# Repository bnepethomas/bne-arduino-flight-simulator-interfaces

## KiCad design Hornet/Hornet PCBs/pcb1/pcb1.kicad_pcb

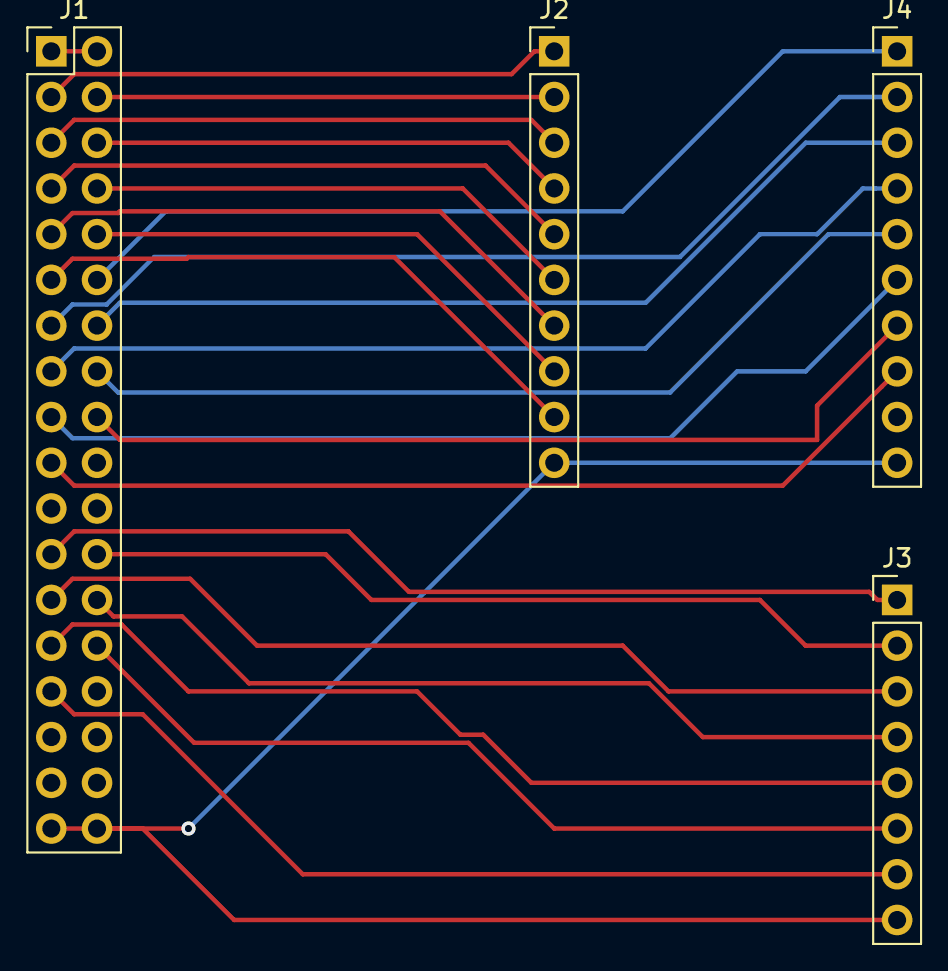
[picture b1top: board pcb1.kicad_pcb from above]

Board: 2 copper layers, 4 parts (0 on the bottom side), 26 nets.

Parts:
J1: Conn_02x18_Odd_Even; PinHeader_2x18_P2.54mm_Vertical
J2, J4: Conn_01x10_Female; PinHeader_1x10_P2.54mm_Vertical
J3: Conn_01x08_Female; PinHeader_1x08_P2.54mm_Vertical

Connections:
+5V: J1.1, J1.2
GND: J1.35, J1.36, J2.10, J3.8, J4.10
unnamed: J1.3, J2.1
unnamed: J1.4, J2.2
unnamed: J1.5, J2.3
unnamed: J1.6, J2.4
unnamed: J1.7, J2.5
unnamed: J1.8, J2.6
unnamed: J1.9, J2.7
unnamed: J1.10, J2.8
unnamed: J1.11, J2.9
unnamed: J1.12, J4.1
unnamed: J1.13, J4.2
unnamed: J1.14, J4.3
unnamed: J1.15, J4.4
unnamed: J1.16, J4.5
unnamed: J1.17, J4.6
unnamed: J1.18, J4.7
unnamed: J1.19, J4.8
unnamed: J1.23, J3.1
unnamed: J1.24, J3.2
unnamed: J1.25, J3.3
unnamed: J1.26, J3.4
unnamed: J1.27, J3.5
unnamed: J1.28, J3.6
unnamed: J1.29, J3.7

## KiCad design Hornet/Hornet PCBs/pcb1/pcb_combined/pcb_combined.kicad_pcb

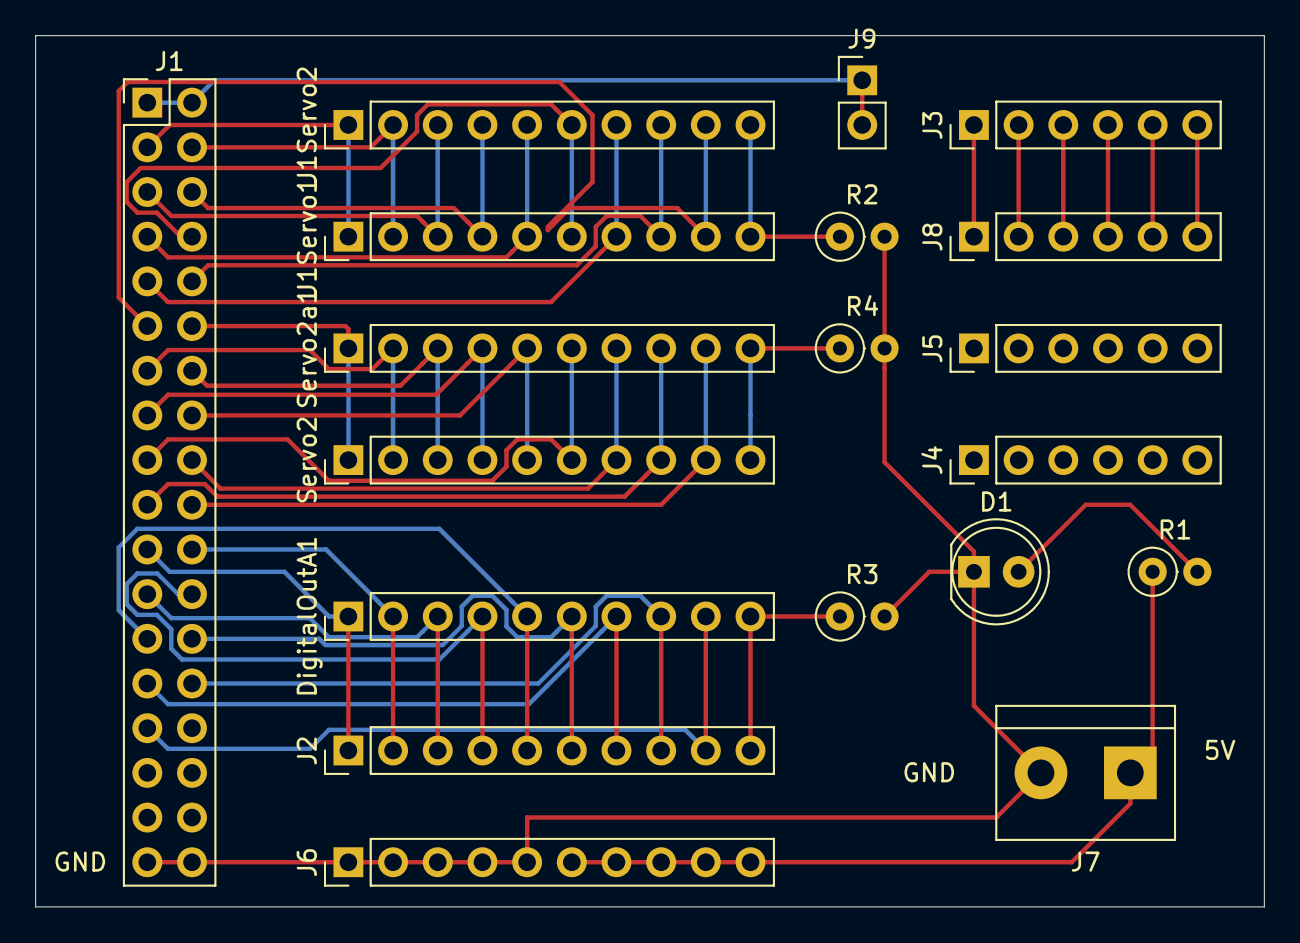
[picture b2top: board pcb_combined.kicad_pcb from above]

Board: 2 copper layers, 69.8 x 49.5 mm, 19 parts (0 on the bottom side), 40 nets.

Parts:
D1: LED; LED_D5.0mm
DigitalOutA1: Digitial Out; PinHeader_1x10_P2.54mm_Vertical
J1: Arduino Mega; PinHeader_2x18_P2.54mm_Vertical
J1Servo1: Servo 1a; PinHeader_1x10_P2.54mm_Vertical
J1Servo2: Servo 1b; PinHeader_1x10_P2.54mm_Vertical
J2: Digital Out; PinHeader_1x10_P2.54mm_Vertical
J3: SPI In; PinHeader_1x06_P2.54mm_Vertical
J4: Spare 1; PinHeader_1x06_P2.54mm_Vertical
J5: Spare 2; PinHeader_1x06_P2.54mm_Vertical
J6: Gnd Pwr; PinHeader_1x10_P2.54mm_Vertical
J7: Aux Pwr In; TerminalBlock_bornier-2_P5.08mm
J8: SPI Out; PinHeader_1x06_P2.54mm_Vertical
J9: Mega 5V; PinHeader_1x02_P2.54mm_Vertical
R1, R2, R3, R4: R_US; R_Axial_DIN0207_L6.3mm_D2.5mm_P2.54mm_Vertical
Servo2: Servo 2; PinHeader_1x10_P2.54mm_Vertical
Servo2a1: Servo 2a; PinHeader_1x10_P2.54mm_Vertical

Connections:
+5V: J6.6, J6.7, J6.8, J6.9, J6.10, J7.1, R1.1
GND: D1.1, J1.35, J1.36, J6.1, J6.2, J6.3, J6.4, J6.5, J7.2, R2.2, R3.2, R4.2
unnamed: D1.2, R1.2
unnamed: DigitalOutA1.1, J1.21, J2.1
unnamed: DigitalOutA1.2, J1.22, J2.2
unnamed: DigitalOutA1.3, J1.23, J2.3
unnamed: DigitalOutA1.4, J1.24, J2.4
unnamed: DigitalOutA1.5, J1.25, J2.5
unnamed: DigitalOutA1.6, J1.26, J2.6
unnamed: DigitalOutA1.7, J1.27, J2.7
unnamed: DigitalOutA1.8, J1.28, J2.8
unnamed: DigitalOutA1.9, J1.29, J2.9
unnamed: DigitalOutA1.10, J2.10, R3.1
unnamed: J1.1, J1.2, J9.1, J9.2
unnamed: J1.3, J1Servo1.1, J1Servo2.1
unnamed: J1.4, J1Servo1.2, J1Servo2.2
unnamed: J1.5, J1Servo1.3, J1Servo2.3
unnamed: J1.6, J1Servo1.4, J1Servo2.4
unnamed: J1.7, J1Servo1.5, J1Servo2.5
unnamed: J1.8, J1Servo1.6, J1Servo2.6
unnamed: J1.9, J1Servo1.7, J1Servo2.7
unnamed: J1.10, J1Servo1.8, J1Servo2.8
unnamed: J1.11, J1Servo1.9, J1Servo2.9
unnamed: J1.12, Servo2.1, Servo2a1.1
unnamed: J1.13, Servo2.2, Servo2a1.2
unnamed: J1.14, Servo2.3, Servo2a1.3
unnamed: J1.15, Servo2.4, Servo2a1.4
unnamed: J1.16, Servo2.5, Servo2a1.5
unnamed: J1.17, Servo2.6, Servo2a1.6
unnamed: J1.18, Servo2.7, Servo2a1.7
unnamed: J1.19, Servo2.8, Servo2a1.8
unnamed: J1.20, Servo2.9, Servo2a1.9
unnamed: J1Servo1.10, J1Servo2.10, R2.1
unnamed: J3.1, J8.1
unnamed: J3.2, J8.2
unnamed: J3.3, J8.3
unnamed: J3.4, J8.4
unnamed: J3.5, J8.5
unnamed: J3.6, J8.6
unnamed: R4.1, Servo2.10, Servo2a1.10

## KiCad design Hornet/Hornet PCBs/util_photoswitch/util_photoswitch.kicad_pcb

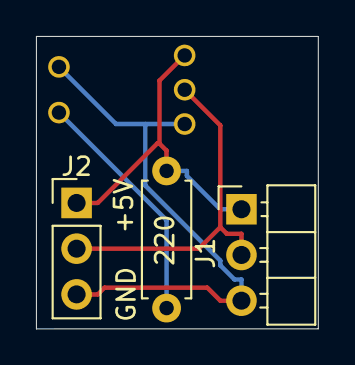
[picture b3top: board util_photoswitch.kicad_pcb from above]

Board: 2 copper layers, 15.7 x 16.2 mm, 4 parts (1 on the bottom side), 4 nets.

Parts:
J1: Conn_01x03_Male; PinHeader_1x03_P2.54mm_Horizontal
J2: Conn_01x03_Male; PinHeader_1x03_P2.54mm_Vertical
R1: 220; R_Axial_DIN0207_L6.3mm_D2.5mm_P7.62mm_Horizontal
U1: OPB615; OPB61x

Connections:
+5V: J1.1, J2.1, R1.2, U1.3 (VCC)
GND: J1.3, J2.3, U1.2 (K), U1.5 (GND)
unnamed: J1.2, J2.2, U1.4 (VOUT)
unnamed: R1.1, U1.1 (A)

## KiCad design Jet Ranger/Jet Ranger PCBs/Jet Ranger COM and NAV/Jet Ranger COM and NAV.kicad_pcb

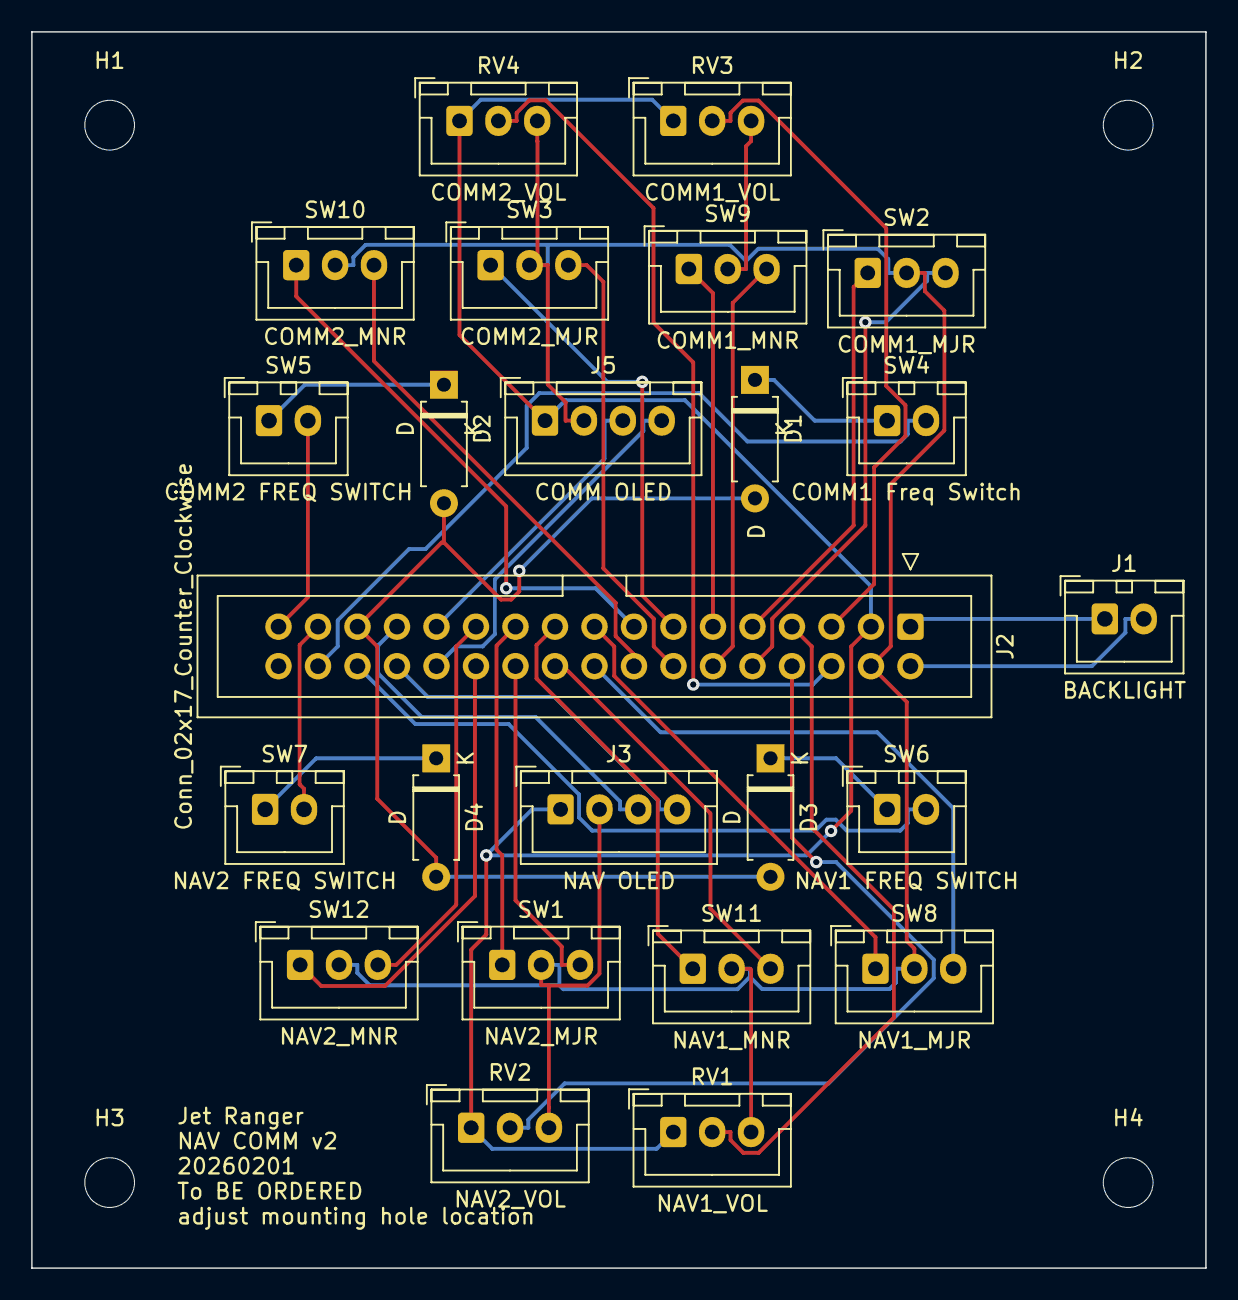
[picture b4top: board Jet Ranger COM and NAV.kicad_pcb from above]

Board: 2 copper layers, 75.5 x 79.5 mm, 28 parts (0 on the bottom side), 37 nets.

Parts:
D1, D2, D3, D4: D; D_A-405_P7.62mm_Horizontal
H1, H2, H3, H4: MountingHole; MountingHole_3.2mm_M3
J1: BACKLIGHT; JST_XH_B2B-XH-A_1x02_P2.50mm_Vertical
J2: Conn_02x17_Counter_Clockwise; IDC-Header_2x17_P2.54mm_Vertical
J3: NAV OLED; JST_XH_B4B-XH-A_1x04_P2.50mm_Vertical
J5: COMM OLED; JST_XH_B4B-XH-A_1x04_P2.50mm_Vertical
RV1: NAV1_VOL; JST_XH_B3B-XH-A_1x03_P2.50mm_Vertical
RV2: NAV2_VOL; JST_XH_B3B-XH-A_1x03_P2.50mm_Vertical
RV3: COMM1_VOL; JST_XH_B3B-XH-A_1x03_P2.50mm_Vertical
RV4: COMM2_VOL; JST_XH_B3B-XH-A_1x03_P2.50mm_Vertical
SW1: NAV2_MJR; JST_XH_B3B-XH-A_1x03_P2.50mm_Vertical
SW2: COMM1_MJR; JST_XH_B3B-XH-A_1x03_P2.50mm_Vertical
SW3: COMM2_MJR; JST_XH_B3B-XH-A_1x03_P2.50mm_Vertical
SW4: COMM1 Freq Switch; JST_XH_B2B-XH-A_1x02_P2.50mm_Vertical
SW5: COMM2 FREQ SWITCH; JST_XH_B2B-XH-A_1x02_P2.50mm_Vertical
SW6: NAV1 FREQ SWITCH; JST_XH_B2B-XH-A_1x02_P2.50mm_Vertical
SW7: NAV2 FREQ SWITCH; JST_XH_B2B-XH-A_1x02_P2.50mm_Vertical
SW8: NAV1_MJR; JST_XH_B3B-XH-A_1x03_P2.50mm_Vertical
SW9: COMM1_MNR; JST_XH_B3B-XH-A_1x03_P2.50mm_Vertical
SW10: COMM2_MNR; JST_XH_B3B-XH-A_1x03_P2.50mm_Vertical
SW11: NAV1_MNR; JST_XH_B3B-XH-A_1x03_P2.50mm_Vertical
SW12: NAV2_MNR; JST_XH_B3B-XH-A_1x03_P2.50mm_Vertical

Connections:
+3.3V: J2.3, J3.1, J5.1, RV1.1, RV2.1, RV3.1, RV4.1
/+12v-IN: J1.1, J2.1
/BACKLIGHT_PANELS: J1.2, J2.2
/COMM1_MJR_A: J2.9, SW2.1
/COMM1_MJR_B: J2.10, SW2.3
/COMM1_MNR_A: J2.11, SW9.1
/COMM1_MNR_B: J2.12, SW9.3
/COMM1_VOL: J2.5, RV3.2
/COMM2_MJR_A: J2.13, SW3.1
/COMM2_MJR_B: J2.14, SW3.3
/COMM2_MNR_A: J2.15, SW10.1
/COMM2_MNR_B: J2.16, SW10.3
/COMM2_VOL: J2.6, RV4.2
/NAV1_MJR_A: J2.17, SW8.1
/NAV1_MJR_B: J2.18, SW8.3
/NAV1_MNR_A: J2.19, SW11.1
/NAV1_MNR_B: J2.20, SW11.3
/NAV1_VOL: J2.7, RV1.2
/NAV2_MJR_B: J2.22, SW1.3
/NAV2_MNR_A: J2.24, SW12.1
/NAV2_MNR_B: J2.23, SW12.3
/NAV2_VOL: J2.8, RV2.2
/NAV2__MJR_A: J2.21, SW1.1
COL0: D1.2 (A), D2.2 (A), D3.2 (A), D4.2 (A), J2.29
COMM_OLED_SC: J2.25, J5.3
COMM_OLED_SD: J2.26, J5.4
GND: J2.4, J3.2, J5.2, RV1.3, RV2.3, RV3.3, RV4.3, SW1.2, SW2.2, SW3.2, SW8.2, SW9.2, SW10.2, SW11.2, SW12.2
NAV_OLED_SC: J2.27, J3.3
NAV_OLED_SD: J2.28, J3.4
unnamed: D1.1 (K), SW4.1
unnamed: D2.1 (K), SW5.1
unnamed: D3.1 (K), SW6.1
unnamed: D4.1 (K), SW7.1
ROW0: J2.30, SW6.2
ROW1: J2.31, SW7.2
ROW2: J2.32, SW4.2
ROW3: J2.33, SW5.2

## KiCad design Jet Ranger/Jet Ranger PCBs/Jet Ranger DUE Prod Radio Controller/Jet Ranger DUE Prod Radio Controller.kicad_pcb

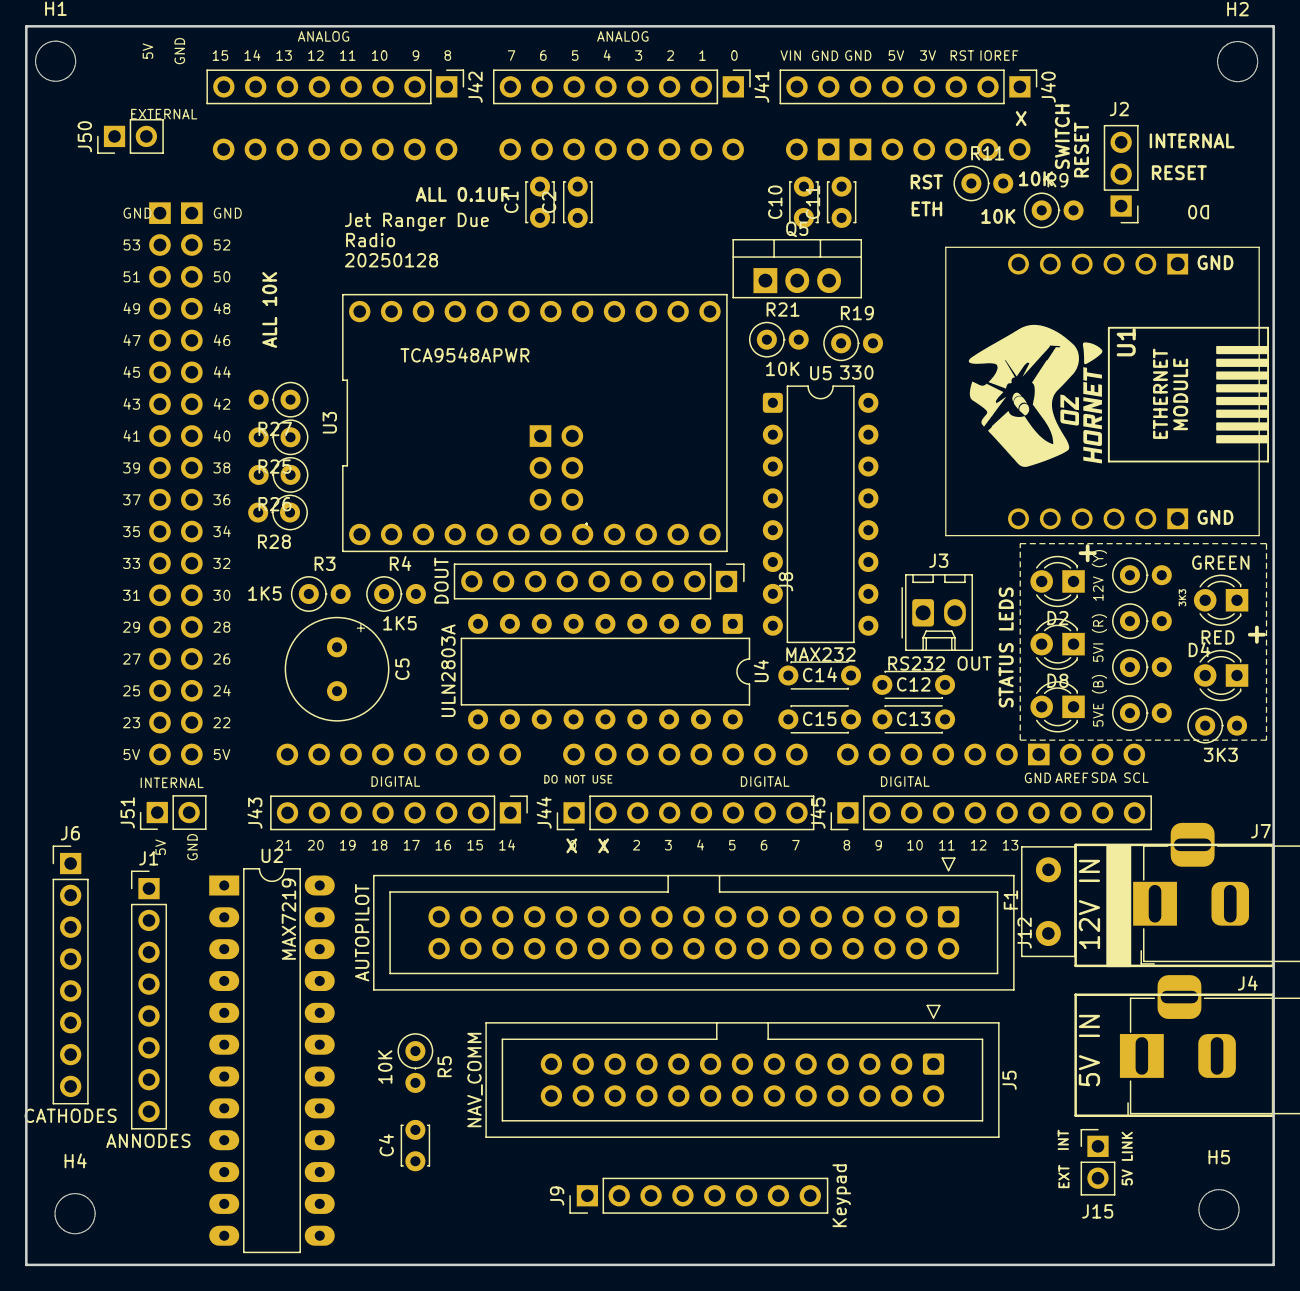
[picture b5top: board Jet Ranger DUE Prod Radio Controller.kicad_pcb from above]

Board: 2 copper layers, 99.5 x 98.8 mm, 62 parts (0 on the bottom side), 130 nets, no tracks yet.

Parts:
A1: Arduino_Mega2560_R3_Shield; Arduino_Due_Shield
C1, C2, C4, C10, C11: 0.1uF; C_Disc_D3.0mm_W2.0mm_P2.50mm
C5: 100uF; C_Radial_D8.0mm_H7.0mm_P3.50mm
C12, C13, C14, C15: 0.1uF; C_Disc_D4.3mm_W1.9mm_P5.00mm
D1: BLUE; LED_D3.0mm
D2: YELLOW; LED_D3.0mm
D3: GREEN; LED_D3.0mm
D4, D8: RED; LED_D3.0mm
F1: Polyfuse; Fuse_Littelfuse_395Series
H1, H5: H1; MountingHole_3.2mm_M3
H2, H4: H2; MountingHole_3.2mm_M3
J1: ANNODES; PinHeader_1x08_P2.54mm_Vertical
J2: Conn_01x03_Pin; PinHeader_1x03_P2.54mm_Vertical
J3: RS232 OUT; Molex_KK-254_AE-6410-02A_1x02_P2.54mm_Vertical
J4: 5V IN; BarrelJack_Horizontal
J5: NAV_COMM; IDC-Header_2x13_P2.54mm_Vertical
J6: CATHODES; PinHeader_1x08_P2.54mm_Vertical
J7: STEPPER IN 12-20VDC; BarrelJack_Horizontal
J8: DOUT; PinHeader_1x09_P2.54mm_Vertical
J9: Keypad; PinHeader_1x08_P2.54mm_Vertical
J12: AUTOPILOT; IDC-Header_2x17_P2.54mm_Vertical
J15, J50, J51: Conn_01x02; PinHeader_1x02_P2.54mm_Vertical
J40, J41, J42, J43, J44: Conn_01x08; PinHeader_1x08_P2.54mm_Vertical
J45: Conn_01x10; PinHeader_1x10_P2.54mm_Vertical
Q5: Q_NMOS_GSD; TO-220-3_Vertical
R1, R2, R7, R8, R12: 3K3; R_Axial_DIN0207_L6.3mm_D2.5mm_P2.54mm_Vertical
R3, R4: 1K5; R_Axial_DIN0207_L6.3mm_D2.5mm_P2.54mm_Vertical
R5, R9, R11, R21, R25, R26, R27, R28: 10K; R_Axial_DIN0207_L6.3mm_D2.5mm_P2.54mm_Vertical
R19: 330; R_Axial_DIN0207_L6.3mm_D2.5mm_P2.54mm_Vertical
U1: USR-ES1; USRES1
U2: MAX7219; DIP-24_W7.62mm_LongPads
U3: TCA9548APWR; AllieExpress_TCA9548A
U4: ULN2803A; DIP-18_W7.62mm
U5: MAX232; DIP-16_W7.62mm

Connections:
+3V3: A1.3V3 (3.3V), J5.3, J12.4, J40.4, R3.1, R4.1, R9.1, U1.B2 (3V3_1), U1.B3 (3V3_2), U3.1 (VCC)
/+5v_IN: C4.1, C5.1, J4.1, J15.2, J50.1, R1.1, R5.2, U2.19 (V+)
/+12v-IN: F1.1, J5.1, J8.1, J12.1, R2.1, U4.10 (COM)
/ALT_A: A1.D46, J12.16
/ALT_B: A1.D47, J12.17
/ANNODE_00: J1.1, J12.5, U2.14 (SEG_A)
/ANNODE_01: J1.2, J12.6, U2.16 (SEG_B)
/ANNODE_02: J1.3, J12.7, U2.20 (SEG_C)
/ANNODE_03: J1.4, J12.8, U2.23 (SEG_D)
/ANNODE_04: J1.5, U2.21 (SEG_E)
/ANNODE_05: J1.6, U2.15 (SEG_F)
/ANNODE_06: J1.7, U2.17 (SEG_G)
/ANNODE_07: J1.8, U2.22 (SEG_DP)
/AP_MAG_SWITCH_COIL: J8.2, J12.3, U4.18 (O1)
/AP_OLED_SC: J12.11, U3.14 (SC2)
/AP_OLED_SD: J12.12, U3.13 (SD2)
/AREF: A1.AREF, J45.8
/BACKLIGHT_PANELS: J5.2, J12.2, Q5.3 (D)
/BACKLIGHT_PWM: A1.D5, J44.6, R19.2
/CATHODE_00: J6.1, J12.9, U2.2 (DIG_0)
/CATHODE_01: J6.2, J12.10, U2.11 (DIG_1)
/CATHODE_02: J6.3, U2.6 (DIG_2)
/CATHODE_03: J6.4, U2.7 (DIG_3)
/CATHODE_04: J6.5, U2.3 (DIG_4)
/CATHODE_05: J6.6, U2.10 (DIG_5)
/CATHODE_06: J6.7, U2.5 (DIG_6)
/CATHODE_07: J6.8, U2.8 (DIG_7)
/COL3: A1.D35, R28.2
/COMM1_A: A1.D36, J5.9
/COMM1_B: A1.D37, J5.10
/COMM1_VOL: A1.A0, C10.1, J5.5, J41.5
/COMM2_A: A1.D38, J5.11
/COMM2_B: A1.D39, J5.12
/COMM2_VOL: A1.A1, C11.1, J5.6, J41.6
/CRS_A: A1.D44, J12.14
/CRS_B: A1.D45, J12.15
/D0: A1.D0 (D0/RX0), J44.1
/D0_OUT: A1.A4, J42.1, U4.1 (I1)
/D1: A1.D1 (D1/TX0), J44.2
/D1_OUT: A1.A5, J42.2, U4.2 (I2)
/D2_OUT: A1.A6, J42.3, U4.3 (I3)
/D3_OUT: A1.A7, J42.4, U4.4 (I4)
/D4_OUT: A1.A8, J42.5, U4.5 (I5)
/D5_OUT: A1.A9, J42.6, U4.6 (I6)
/D6_OUT: A1.A10, J42.7, U4.7 (I7)
/D7_OUT: A1.A11, J42.8, U4.8 (I8)
/GPS_TX: A1.D18 (D18/TX1), J43.5, U5.11 (T1IN)
/GREEN_LED: A1.D14 (D14/TX3), J43.1, R7.1
/HDG_A: A1.D28, J12.21
/HDG_B: A1.D29, J12.20
/I2C_SEL_A0: A1.D4 (D4_CS1), J44.5, U3.6 (A0)
/I2C_SEL_A1: A1.D3, J44.4, U3.7 (A1)
/I2C_SEL_A2: A1.D2, J44.3, U3.8 (A2)
/IAS_A: A1.D27, J12.22
/IAS_B: A1.D26, J12.23
/INT_5V: A1.5V1 (5V), A1.5V3 (5V), A1.5V4 (5V), J15.1, J40.5, J51.1, R11.1, R12.1, R25.1, R26.1, R27.1, R28.1, U5.16 (VCC)
/IORF: A1.IORF (IOREF), J40.2
/Keypad Col 0: A1.D11, J9.5, J45.4
/Keypad Col 1: A1.D12, J9.6, J45.5
/Keypad Col 2: A1.D13, J9.7, J45.6
/Keypad Row 0: A1.D6, J9.1, J44.7
/Keypad Row 1: A1.D7, J9.2, J44.8
/Keypad Row 2: A1.D8, J9.3, J45.1
/Keypad Row 3: A1.D9, J9.4, J45.2
/MAX_7219-CLOCK: A1.D51, U2.13 (CLK)
/MAX_7219-DIN: A1.D52 (D52_CS2), U2.1 (DIN)
/MAX_7219-LOAD: A1.D50, U2.12 (LOAD)
/NAV1_A: A1.D40, J5.13
/NAV1_B: A1.D41, J5.14
/NAV1_VOL: A1.A2, C1.1, J5.7, J41.7
/NAV2_A: A1.D42, J5.15
/NAV2_B: A1.D43, J5.16
/NAV2_VOL: A1.A3, C2.1, J5.8, J41.8
/PIN_20: A1.D20 (D20/SDA), J43.7
/PIN_21: A1.D21 (D21/SCL), J43.8
/RED_LED: A1.D15 (D15/RX3), J43.2, R8.1
/RESET: A1.RST1 (RESET), J2.2, J40.3, R11.2
/RESET_pin: A1.D49, J2.3
/VIN: A1.VIN, J40.8
/VS_A: A1.D30, J12.19
/VS_B: A1.D31, J12.18
COL0: A1.D32, J5.21, R25.2
COL1: A1.D33, J12.24, R26.2
COL2: A1.D34, J12.25, R27.2
COMM_OLED_SC: J5.17, U3.12 (SC1)
COMM_OLED_SD: J5.18, U3.11 (SD1)
ES1_RST: A1.D53, U1.B5 (RST), U3.5 (~RESET)
GND: A1.GND1 (GND), A1.GND2 (GND), A1.GND3 (GND), A1.GND5 (GND), A1.GND6 (GND), C1.2, C2.2, C4.2, C5.2, C10.2, C11.2, C14.2, C15.2, D1.2 (K), D2.2 (K), D3.2 (K), D4.2 (K), D8.2 (K), J2.1, J3.2, J4.2, J5.4, J7.2, J12.13, J40.6, J40.7, J45.7, J50.2, J51.2, Q5.2 (S), R21.1, U1.A1 (GND_1), U1.A2 (GND_2), U1.B1 (GND_3), U2.4 (GND), U2.9 (GND), U3.2 (GND), U4.9 (GND), U5.15 (GND)
MISO: A1.MISO (SPI_MISO), U1.B6 (MISO)
MOSI: A1.MOSI (SPI_MOSI), U1.A3 (MOSI)
NAV_OLED_SC: J5.20, U3.10 (SC0)
NAV_OLED_SD: J5.19, U3.9 (SD0)
unnamed: A1.CANR (CANRX), J41.1
unnamed: A1.CANT (CANTX), J41.2
unnamed: A1.D16 (D16/TX2), J43.3
unnamed: A1.D17 (D17/RX2), J43.4
unnamed: A1.D19 (D19/RX1), J43.6
unnamed: D1.1 (A), R1.2
unnamed: D2.1 (A), R2.2
unnamed: D3.1 (A), R7.2
unnamed: D4.1 (A), R8.2
unnamed: D8.1 (A), R12.2
unnamed: J3.1, U5.14 (T1OUT)
unnamed: F1.2, J7.1
unnamed: J8.3, U4.17 (O2)
unnamed: J8.4, U4.16 (O3)
unnamed: J8.5, U4.15 (O4)
unnamed: J8.6, U4.14 (O5)
unnamed: J8.7, U4.13 (O6)
unnamed: J8.8, U4.12 (O7)
unnamed: J8.9, U4.11 (O8)
unnamed: A1.DAC0, J41.3
unnamed: A1.DAC1, J41.4
unnamed: Q5.1 (G), R19.1, R21.2
unnamed: R9.2, U1.A6 (INT)
unnamed: R5.1, U2.18 (ISET)
unnamed: C12.1, U5.1 (C1+)
unnamed: C12.2, U5.3 (C1-)
unnamed: C13.1, U5.4 (C2+)
unnamed: C13.2, U5.5 (C2-)
unnamed: C15.1, U5.2 (VS+)
unnamed: C14.1, U5.6 (VS-)
ROW0: A1.D22, J5.22, J12.26
ROW1: A1.D23, J5.23, J12.27
ROW2: A1.D24, J5.24, J12.28
ROW3: A1.D25, J5.25, J12.29
SCL: A1.SCL1, J45.10, R3.2, U3.4 (SCL)
SCLK: A1.SCK (SPI_SCK), U1.A4 (SCLK)
SDA: A1.SDA1, J45.9, R4.2, U3.3 (SDA)
SS: A1.D10 (D10_CS0), J45.3, U1.A5 (CS)

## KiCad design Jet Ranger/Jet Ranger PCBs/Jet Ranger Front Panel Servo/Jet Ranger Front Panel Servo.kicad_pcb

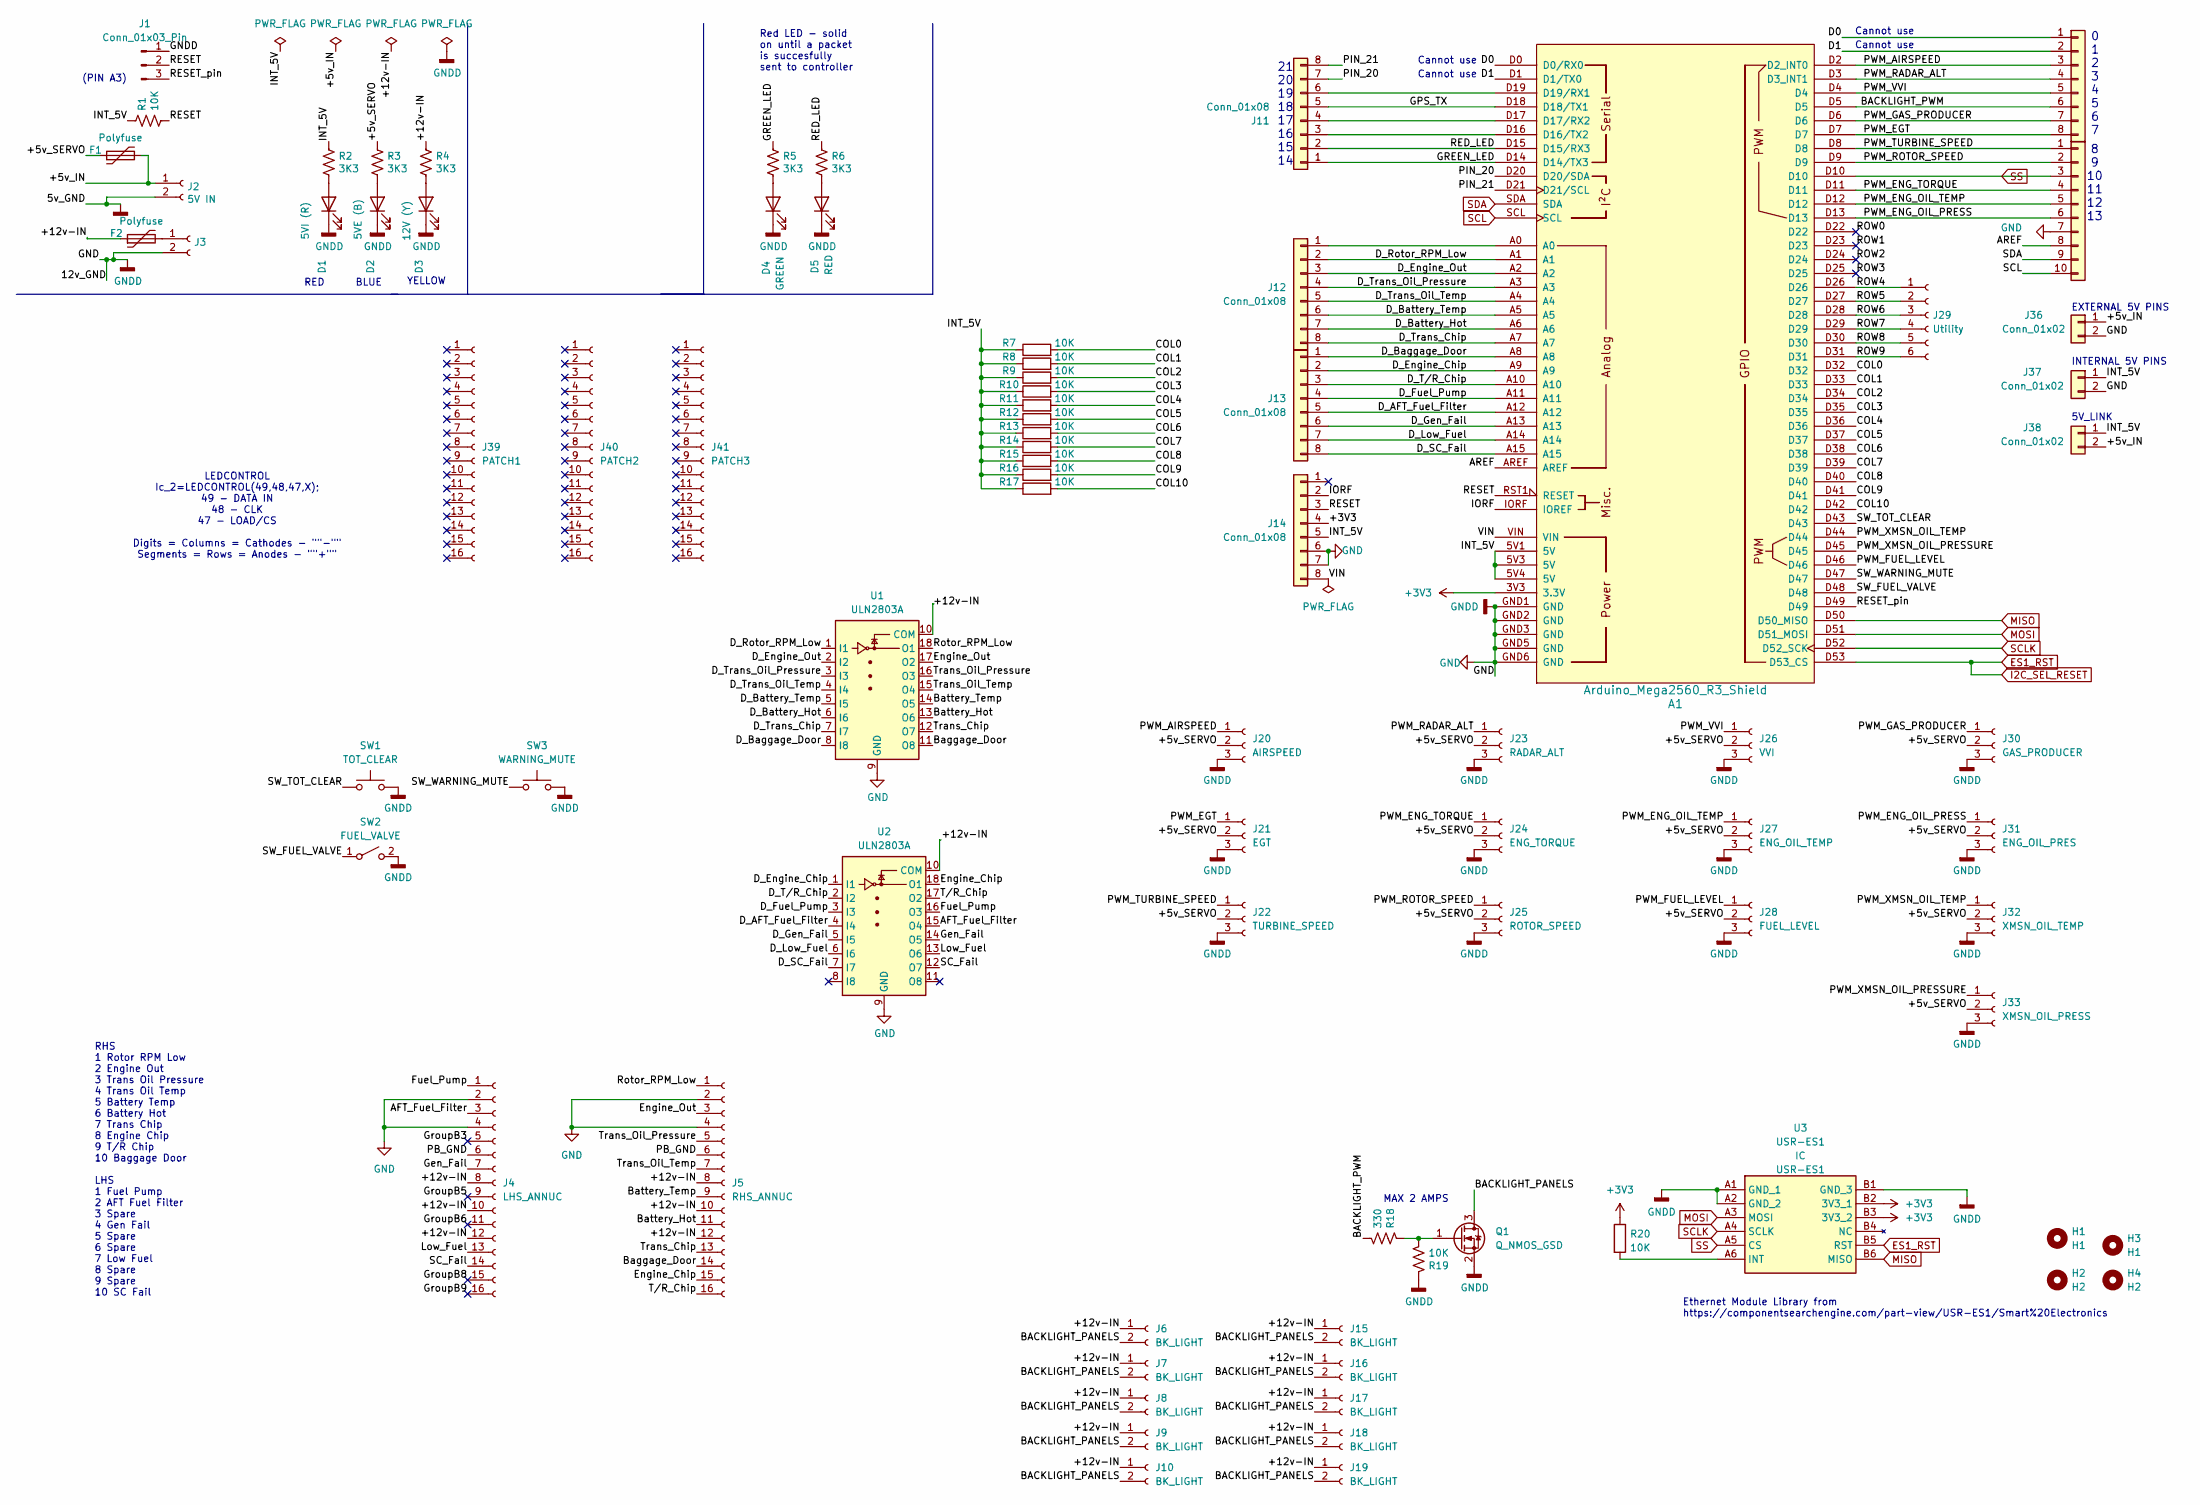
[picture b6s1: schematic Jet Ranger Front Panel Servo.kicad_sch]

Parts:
A1: Arduino_Mega2560_R3_Shield
D1: 5VI (R); LED_D3.0mm
D2: 5VE (B); LED_D3.0mm
D3: 12V (Y); LED_D3.0mm
D4: GREEN; LED_D3.0mm
D5: RED; LED_D3.0mm
F1, F2: Polyfuse; Fuse_Littelfuse_395Series
H1, H3: H1; MountingHole_3.2mm_M3
H2, H4: H2; MountingHole_3.2mm_M3
J1: Conn_01x03_Pin; PinHeader_1x03_P2.54mm_Vertical
J2: 5V IN; BarrelJack_Horizontal
J3: STEPPER IN 12-20VDC; BarrelJack_Horizontal
J4: LHS_ANNUC; IDC-Header_2x08_P2.54mm_Vertical
J5: RHS_ANNUC; IDC-Header_2x08_P2.54mm_Vertical
J6, J7, J8, J9, J10, J15, J16, J17, J18, J19: BK_LIGHT; Molex_KK-254_AE-6410-02A_1x02_P2.54mm_Vertical
J11, J12, J13, J14, J34: Conn_01x08; PinHeader_1x08_P2.54mm_Vertical
J20: AIRSPEED; PinHeader_1x03_P2.54mm_Vertical
J21: EGT; PinHeader_1x03_P2.54mm_Vertical
J22: TURBINE_SPEED; PinHeader_1x03_P2.54mm_Vertical
J23: RADAR_ALT; PinHeader_1x03_P2.54mm_Vertical
J24: ENG_TORQUE; PinHeader_1x03_P2.54mm_Vertical
J25: ROTOR_SPEED; PinHeader_1x03_P2.54mm_Vertical
J26: VVI; PinHeader_1x03_P2.54mm_Vertical
J27: ENG_OIL_TEMP; PinHeader_1x03_P2.54mm_Vertical
J28: FUEL_LEVEL; PinHeader_1x03_P2.54mm_Vertical
J29: Utility; PinHeader_1x06_P2.54mm_Vertical
J30: GAS_PRODUCER; PinHeader_1x03_P2.54mm_Vertical
J31: ENG_OIL_PRES; PinHeader_1x03_P2.54mm_Vertical
J32: XMSN_OIL_TEMP; PinHeader_1x03_P2.54mm_Vertical
J33: XMSN_OIL_PRESS; PinHeader_1x03_P2.54mm_Vertical
J35: Conn_01x10; PinHeader_1x10_P2.54mm_Vertical
J36, J37, J38: Conn_01x02; PinHeader_1x02_P2.54mm_Vertical
J39: PATCH1; PinHeader_1x16_P2.54mm_Vertical
J40: PATCH2; PinHeader_1x16_P2.54mm_Vertical
J41: PATCH3; PinHeader_1x16_P2.54mm_Vertical
Q1: Q_NMOS_GSD; TO-220-3_Vertical
R1, R7, R8, R9, R10, R11, R12, R13, R14, R15, R16, R17, R19, R20: 10K; R_Axial_DIN0207_L6.3mm_D2.5mm_P2.54mm_Vertical
R2, R3, R4, R5, R6: 3K3; R_Axial_DIN0207_L6.3mm_D2.5mm_P2.54mm_Vertical
R18: 330; R_Axial_DIN0207_L6.3mm_D2.5mm_P2.54mm_Vertical
SW1: TOT_CLEAR; Molex_KK-254_AE-6410-02A_1x02_P2.54mm_Vertical
SW2: FUEL_VALVE; Molex_KK-254_AE-6410-02A_1x02_P2.54mm_Vertical
SW3: WARNING_MUTE; Molex_KK-254_AE-6410-02A_1x02_P2.54mm_Vertical
U1, U2: ULN2803A; DIP-18_W7.62mm
U3: USR-ES1; USRES1; Manufacturer_Part_Number USR-ES1

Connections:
+3V3: A1.3V3 (3.3V), J14.4, R20.1, U3.B2 (3V3_1), U3.B3 (3V3_2)
/+5v_IN: F1.2, J2.1, J36.1, J38.2
/+5v_SERVO: F1.1, J20.2, J21.2, J22.2, J23.2, J24.2, J25.2, J26.2, J27.2, J28.2, J30.2, J31.2, J32.2, J33.2, R3.1
/+12v-IN: F2.1, J4.8, J4.10, J4.12, J5.8, J5.10, J5.12, J6.1, J7.1, J8.1, J9.1, J10.1, J15.1, J16.1, J17.1, J18.1, J19.1, R4.1, U1.10 (COM), U2.10 (COM)
/AFT_Fuel_Filter: J4.3, U2.15 (O4)
/AREF: A1.AREF, J35.8
/BACKLIGHT_PANELS: J6.2, J7.2, J8.2, J9.2, J10.2, J15.2, J16.2, J17.2, J18.2, J19.2, Q1.3 (D)
/BACKLIGHT_PWM: A1.D5, J34.6, R18.2
/Baggage_Door: J5.14, U1.11 (O8)
/Battery_Hot: J5.11, U1.13 (O6)
/Battery_Temp: J5.9, U1.14 (O5)
/COL0: A1.D32, R7.2
/COL1: A1.D33, R8.2
/COL2: A1.D34, R9.2
/COL3: A1.D35, R10.2
/COL4: A1.D36, R11.2
/COL5: A1.D37, R12.2
/COL6: A1.D38, R13.2
/COL7: A1.D39, R14.2
/COL8: A1.D40, R15.2
/COL9: A1.D41, R16.2
/COL10: A1.D42, R17.2
/D0: A1.D0 (D0/RX0), J34.1
/D1: A1.D1 (D1/TX0), J34.2
/D_AFT_Fuel_Filter: A1.A12, J13.5, U2.4 (I4)
/D_Baggage_Door: A1.A8, J13.1, U1.8 (I8)
/D_Battery_Hot: A1.A6, J12.7, U1.6 (I6)
/D_Battery_Temp: A1.A5, J12.6, U1.5 (I5)
/D_Engine_Chip: A1.A9, J13.2, U2.1 (I1)
/D_Engine_Out: A1.A2, J12.3, U1.2 (I2)
/D_Fuel_Pump: A1.A11, J13.4, U2.3 (I3)
/D_Gen_Fail: A1.A13, J13.6, U2.5 (I5)
/D_Low_Fuel: A1.A14, J13.7, U2.6 (I6)
/D_Rotor_RPM_Low: A1.A1, J12.2, U1.1 (I1)
/D_SC_Fail: A1.A15, J13.8, U2.7 (I7)
/D_Trans_Chip: A1.A7, J12.8, U1.7 (I7)
/D_Trans_Oil_Pressure: A1.A3, J12.4, U1.3 (I3)
/D_Trans_Oil_Temp: A1.A4, J12.5, U1.4 (I4)
/D_T/R_Chip: A1.A10, J13.3, U2.2 (I2)
/Engine_Chip: J5.15, U2.18 (O1)
/Engine_Out: J5.3, U1.17 (O2)
/Fuel_Pump: J4.1, U2.16 (O3)
/GPS_TX: A1.D18 (D18/TX1), J11.5
/GREEN_LED: A1.D14 (D14/TX3), J11.1, R5.1
/Gen_Fail: J4.7, U2.14 (O5)
/GroupB3: J4.5
/GroupB5: J4.9
/GroupB6: J4.11
/GroupB8: J4.15
/GroupB9: J4.16
/INT_5V: A1.5V1 (5V), A1.5V3 (5V), A1.5V4 (5V), J14.5, J37.1, J38.1, R1.1, R2.1, R7.1, R8.1, R9.1, R10.1, R11.1, R12.1, R13.1, R14.1, R15.1, R16.1, R17.1
/IORF: A1.IORF (IOREF), J14.2
/Low_Fuel: J4.13, U2.13 (O6)
/PB_GND: J4.6, J5.6
/PIN_20: A1.D20 (D20/SDA), J11.7
/PIN_21: A1.D21 (D21/SCL), J11.8
/PWM_AIRSPEED: A1.D2 (D2_INT0), J20.1, J34.3
/PWM_EGT: A1.D7, J21.1, J34.8
/PWM_ENG_OIL_PRESS: A1.D13, J31.1, J35.6
/PWM_ENG_OIL_TEMP: A1.D12, J27.1, J35.5
/PWM_ENG_TORQUE: A1.D11, J24.1, J35.4
/PWM_FUEL_LEVEL: A1.D46, J28.1
/PWM_GAS_PRODUCER: A1.D6, J30.1, J34.7
/PWM_RADAR_ALT: A1.D3 (D3_INT1), J23.1, J34.4
/PWM_ROTOR_SPEED: A1.D9, J25.1, J35.2
/PWM_TURBINE_SPEED: A1.D8, J22.1, J35.1
/PWM_VVI: A1.D4, J26.1, J34.5
/PWM_XMSN_OIL_PRESSURE: A1.D45, J33.1
/PWM_XMSN_OIL_TEMP: A1.D44, J32.1
/RED_LED: A1.D15 (D15/RX3), J11.2, R6.1
/RESET: A1.RST1 (RESET), J1.2, J14.3, R1.2
/RESET_pin: A1.D49, J1.3
/ROW0: A1.D22
/ROW1: A1.D23
/ROW2: A1.D24
/ROW3: A1.D25
/ROW4: A1.D26, J29.1
/ROW5: A1.D27, J29.2
/ROW6: A1.D28, J29.3
/ROW7: A1.D29, J29.4
/ROW8: A1.D30, J29.5
/ROW9: A1.D31, J29.6
/Rotor_RPM_Low: J5.1, U1.18 (O1)
/SC_Fail: J4.14, U2.12 (O7)
/SW_FUEL_VALVE: A1.D48, SW2.1 (A)
/SW_TOT_CLEAR: A1.D43, SW1.1
/SW_WARNING_MUTE: A1.D47, SW3.1
/Trans_Chip: J5.13, U1.12 (O7)
/Trans_Oil_Pressure: J5.5, U1.16 (O3)
/Trans_Oil_Temp: J5.7, U1.15 (O4)
/T/R_Chip: J5.16, U2.17 (O2)
/VIN: A1.VIN, J14.8
ES1_RST: A1.D53 (D53_CS), U3.B5 (RST)
GND: A1.GND1 (GND), A1.GND2 (GND), A1.GND3 (GND), A1.GND5 (GND), A1.GND6 (GND), D1.1 (K), D2.1 (K), D3.1 (K), D4.1 (K), D5.1 (K), J1.1, J2.2, J3.2, J4.2, J4.4, J5.2, J5.4, J14.6, J14.7, J20.3, J21.3, J22.3, J23.3, J24.3, J25.3, J26.3, J27.3, J28.3, J30.3, J31.3, J32.3, J33.3, J35.7, J36.2, J37.2, Q1.2 (S), R19.1, SW1.2, SW2.2 (B), SW3.2, U1.9 (GND), U2.9 (GND), U3.A1 (GND_1), U3.A2 (GND_2), U3.B1 (GND_3)
MISO: A1.D50 (D50_MISO), U3.B6 (MISO)
MOSI: A1.D51 (D51_MOSI), U3.A3 (MOSI)
unnamed: A1.D16 (D16/TX2), J11.3
unnamed: A1.D17 (D17/RX2), J11.4
unnamed: A1.D19 (D19/RX1), J11.6
unnamed: D1.2 (A), R2.2
unnamed: D2.2 (A), R3.2
unnamed: D3.2 (A), R4.2
unnamed: D4.2 (A), R5.2
unnamed: D5.2 (A), R6.2
unnamed: F2.2, J3.1
unnamed: A1.A0, J12.1
unnamed: Q1.1 (G), R18.1, R19.2
unnamed: R20.2, U3.A6 (INT)
SCL: A1.SCL, J35.10
SCLK: A1.D52 (D52_SCK), U3.A4 (SCLK)
SDA: A1.SDA, J35.9
SS: A1.D10, J35.3, U3.A5 (CS)

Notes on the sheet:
YELLOW
MAX 2 AMPS
BLUE
INTERNAL 5V PINS
Ethernet Module Library from https://componentsearchengine.com/part-view/USR-ES1/Smart%20Electronics
Cannot use
RED
(PIN A3)
0 1 2 3 4 5 6 7
LEDCONTROL Ic_2=LEDCONTROL(49,48,47,X); 49 - DATA IN 48 - CLK 47 - LOAD/CS Digits = Columns = Cathodes - ""-"" Segments = Rows = Anodes - ""+""
Red LED - solid on until a packet is succesfully sent to controller
RHS 1 Rotor RPM Low 2 Engine Out 3 Trans Oil Pressure 4 Trans Oil Temp 5 Battery Temp 6 Battery Hot 7 Trans Chip 8 Engine Chip 9 T/R Chip 10 Baggage Door LHS 1 Fuel Pump 2 AFT Fuel Filter 3 Spare 4 Gen Fail 5 Spare 6 Spare 7 Low Fuel 8 Spare 9 Spare 10 SC Fail
5V_LINK
21 20 19 18 17 16 15 14
EXTERNAL 5V PINS
8 9 10 11 12 13

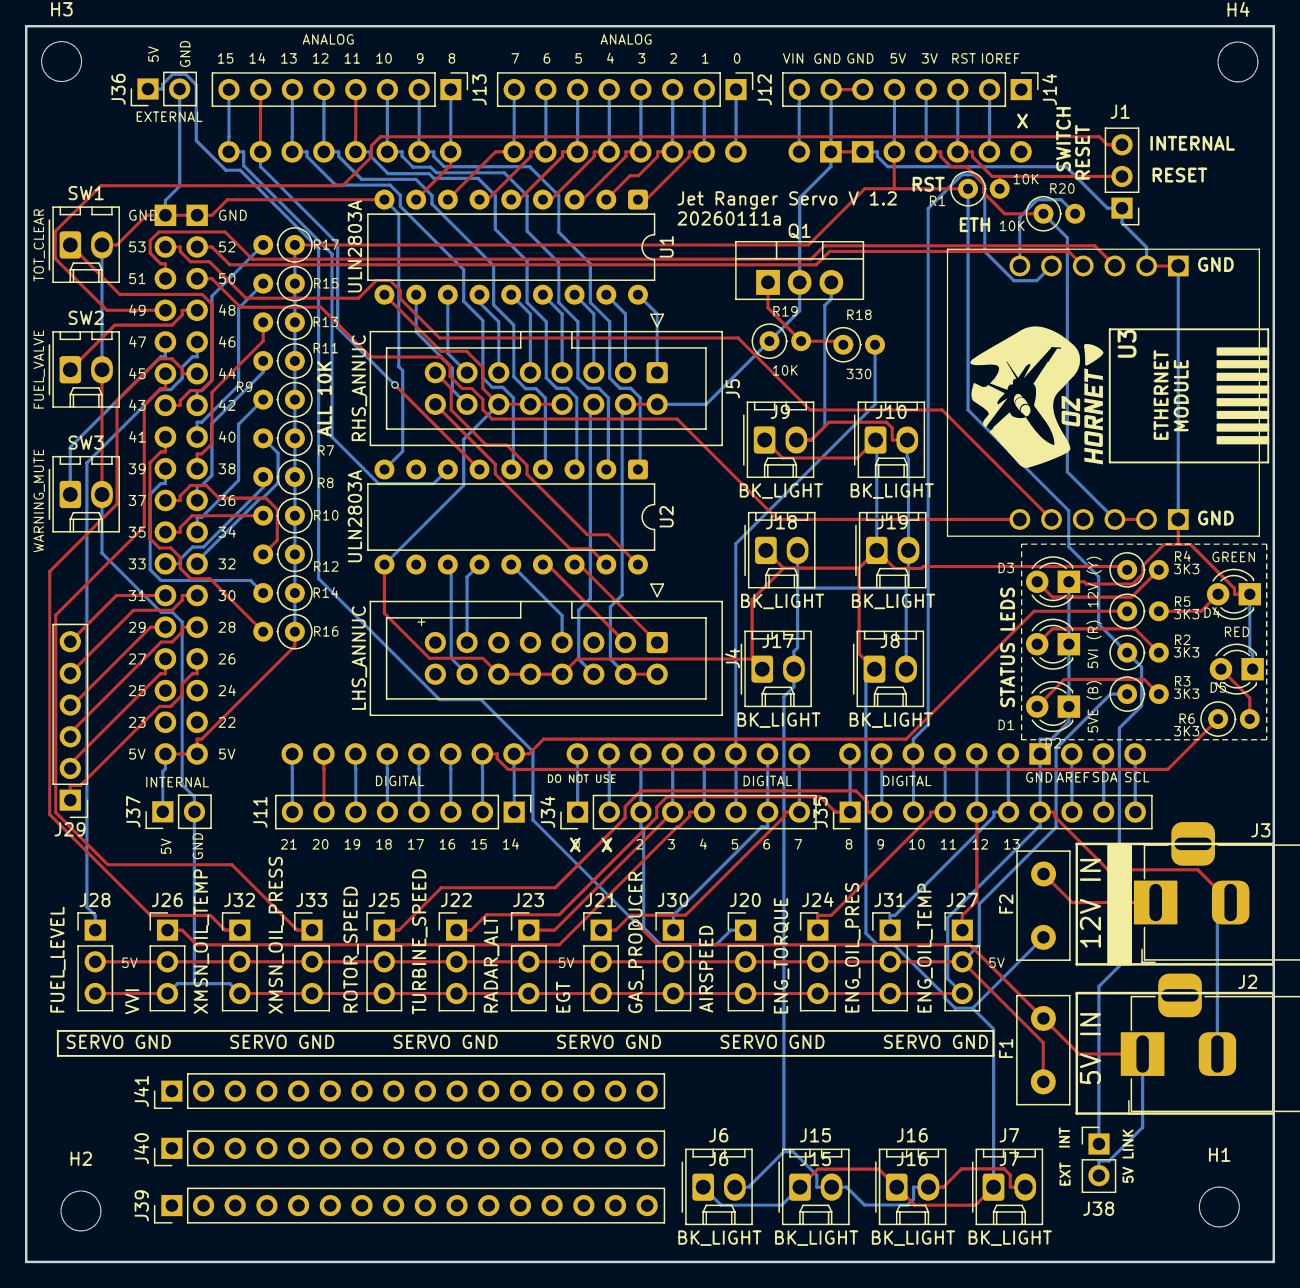
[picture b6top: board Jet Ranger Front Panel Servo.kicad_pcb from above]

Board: 2 copper layers, 100.0 x 99.1 mm, 80 parts (0 on the bottom side), 103 nets.

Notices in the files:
Jet Ranger/Jet Ranger PCBs/Jet Ranger Front Panel Servo/Jet Ranger Front Panel Servo.kicad_pcb:
© OZ HORNET
